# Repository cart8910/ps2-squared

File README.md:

# ps2-squared
Dead simple PS2 power supply replacement (with optional USB-C!)

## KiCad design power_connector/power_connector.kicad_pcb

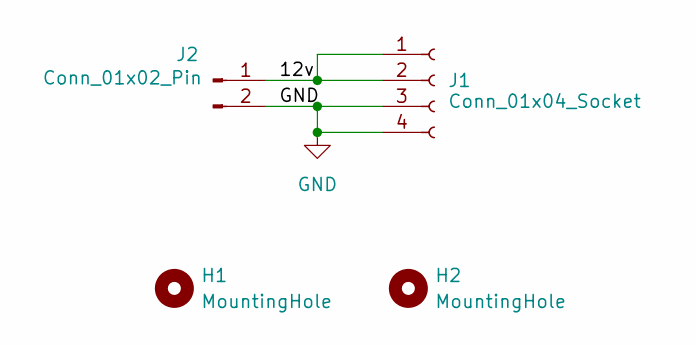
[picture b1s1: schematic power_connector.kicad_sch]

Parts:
H1, H2: MountingHole; MountingHole_2.2mm_M2
J1: Conn_01x04_Socket; JST_NV_B04P-NV_1x04_P5.00mm_Vertical
J2: Conn_01x02_Pin; JST_NV_B02P-NV_1x02_P5.00mm_Vertical

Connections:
/12v: J1.1, J1.2, J2.1
GND: J1.3, J1.4, J2.2

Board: 2 copper layers, 4 parts (0 on the bottom side), 2 nets, no tracks yet.

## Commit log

2026-05-27 first commit - began pcb work
2026-06-15 mounting holes and board outline
2026-06-23 final
